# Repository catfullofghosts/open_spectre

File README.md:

# OPEN_SPECTRE ✨
FPGA recreation of the EMS SPECTRE video synth.

Sorry about the repo disappearing for a while. Had some issues, it's back now.

Open to donations and contributors with FPGA experience.

> The EMS Sprectre video synthesiser was a unique and revolutionary product for its time (late 1970's): an instrument capable of producing exciting graphic images on an ordinary television screen. The complete SPECTRE package consists of the synthesiser itself, plus a Sony Trinitron colour monitor and a Sony black-and-white TV camera. The synthesiser was compact (38"x23.5"x7"), portable (about 35 pounds/15.9KG), and unequalled in its simplicity and versatility.

## Status (on an Arty Z7-20)

`overall progress is: it runs!, but still lots of little things to do`

| block | state | notes |
| --- | --- | --- |
| HDMI in / out | done | Digilent Arty Z7-20, input works! output is at 720P |
| digital matrix | done |  |
| analog matrix | done | need to merge signed branch in. |
| oscillators | done | vert sync still a bit blocky, why? |
| shape gen | almost done | needs compare with original|
| colour encode | done | |
| audio in | wip | working, but needs propper testing|
| Vitis test software | done | video in works, frame buffer works, midi parsing works |
| Pico Based midi usb in | done | is just a bridge (computer -> pico (usb midi) -> uart -> zynq |
| hardware interface | not started | still software controlled |

## Aim

Recreate the SPECTRE in HDL so it can stay true to the original design. Then expand on the design in the same spirit as the original.
The idea is preservation, but not at the cost of usability and modern quality of life things (like digital video in and out, or MIDI control)

More on that: [Cloning Hardware Ethos](documentation/Cloning%20a%20process%20not%20a%20device.md)

## FPGA build
- [How to build with Vivado 2024.2 / `build.bat`](fpga/readme.md)

## Want to contribute?

If you have FPGA and/or Verilog/VHDL skills, industrial design skills or VST building skills, I/we would love to have you involved. PLZ!!!!!. A few things first.

### What to do first
- Look through [Spectron Resources](Spectron%20Resources/readme.md) to get an idea of what the EMS SPECTRE is and how it works
- Look at the [top-level diagram](documentation/ems_diagram.drawio) and the [list of modules](documentation/readme.md)
- HDL lives in [`fpga/src`](fpga/src/readme.md) — top is `spector_wrapper_zynq_B.vhd`

### Project details
- RTL in VHDL or Verilog (VHDL preferred, no SystemVerilog sorry)
- One module per file with a separate testbench (Verilog or VHDL testbenches only — not everything has one yet, but it should)
- Testbenches should print a message at the end confirming pass or fail
- No HLS or auto-generated code, no busses or interfaces for now (will be busses later)
- Use any software you like, but a Vivado project is supplied
- Follow the template for file headers and comments
- Follow the folder structure for the project
- Contributions need to be something we can release under CC BY-NC

### How to get involved
- Email *OPEN.SPECTRE.PROJECT@gmail.com* and see what modules/work we need at the moment
- Branch the repo, make a module, and submit a pull request
- If you are not good at git/GitHub, write the module and email it to us. We will integrate it.

## License
Creative Commons CC BY-NC
* I want everyone to be able to experience this seminal (ewwww...) video synth and learn from its design and technical wizardry....... buuuuut, I want to make a physical product version of this one day, so hence the NC. That said if you want to do some thing commercial with this code, just email me about it and I'll most likely just say yes.

## Contributors
- Remi Freer
- Jacob Stoker
- Andrey Demenev
- Robert D Jordan

## Donations
We are very thankful to have received donations from the following people:
Chris Korvin,
Jay Hotchin,
Milton Grimshaw, 
and more amazing anonymous people.

## Thank yous
- MESS Melbourne
  - Sam Galyer
  - Robin Fox
- Flo Kaufmann
- Violet Shylet

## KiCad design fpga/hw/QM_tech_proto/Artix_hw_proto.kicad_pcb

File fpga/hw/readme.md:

using this dev board:
https://www.aliexpress.com/item/1005005961199362.html?spm=a2g0o.order_list.order_list_main.76.1cc71802oC4QSS
https://github.com/ChinaQMTECH/QMTECH_XC7A15T_35T_CSG325_CORE_BOARD

use these libs
https://github.com/jmwilson/Adafruit-GFX-Library_MicroBlaze
https://github.com/jmwilson/Adafruit_SSD1306_MicroBlaze

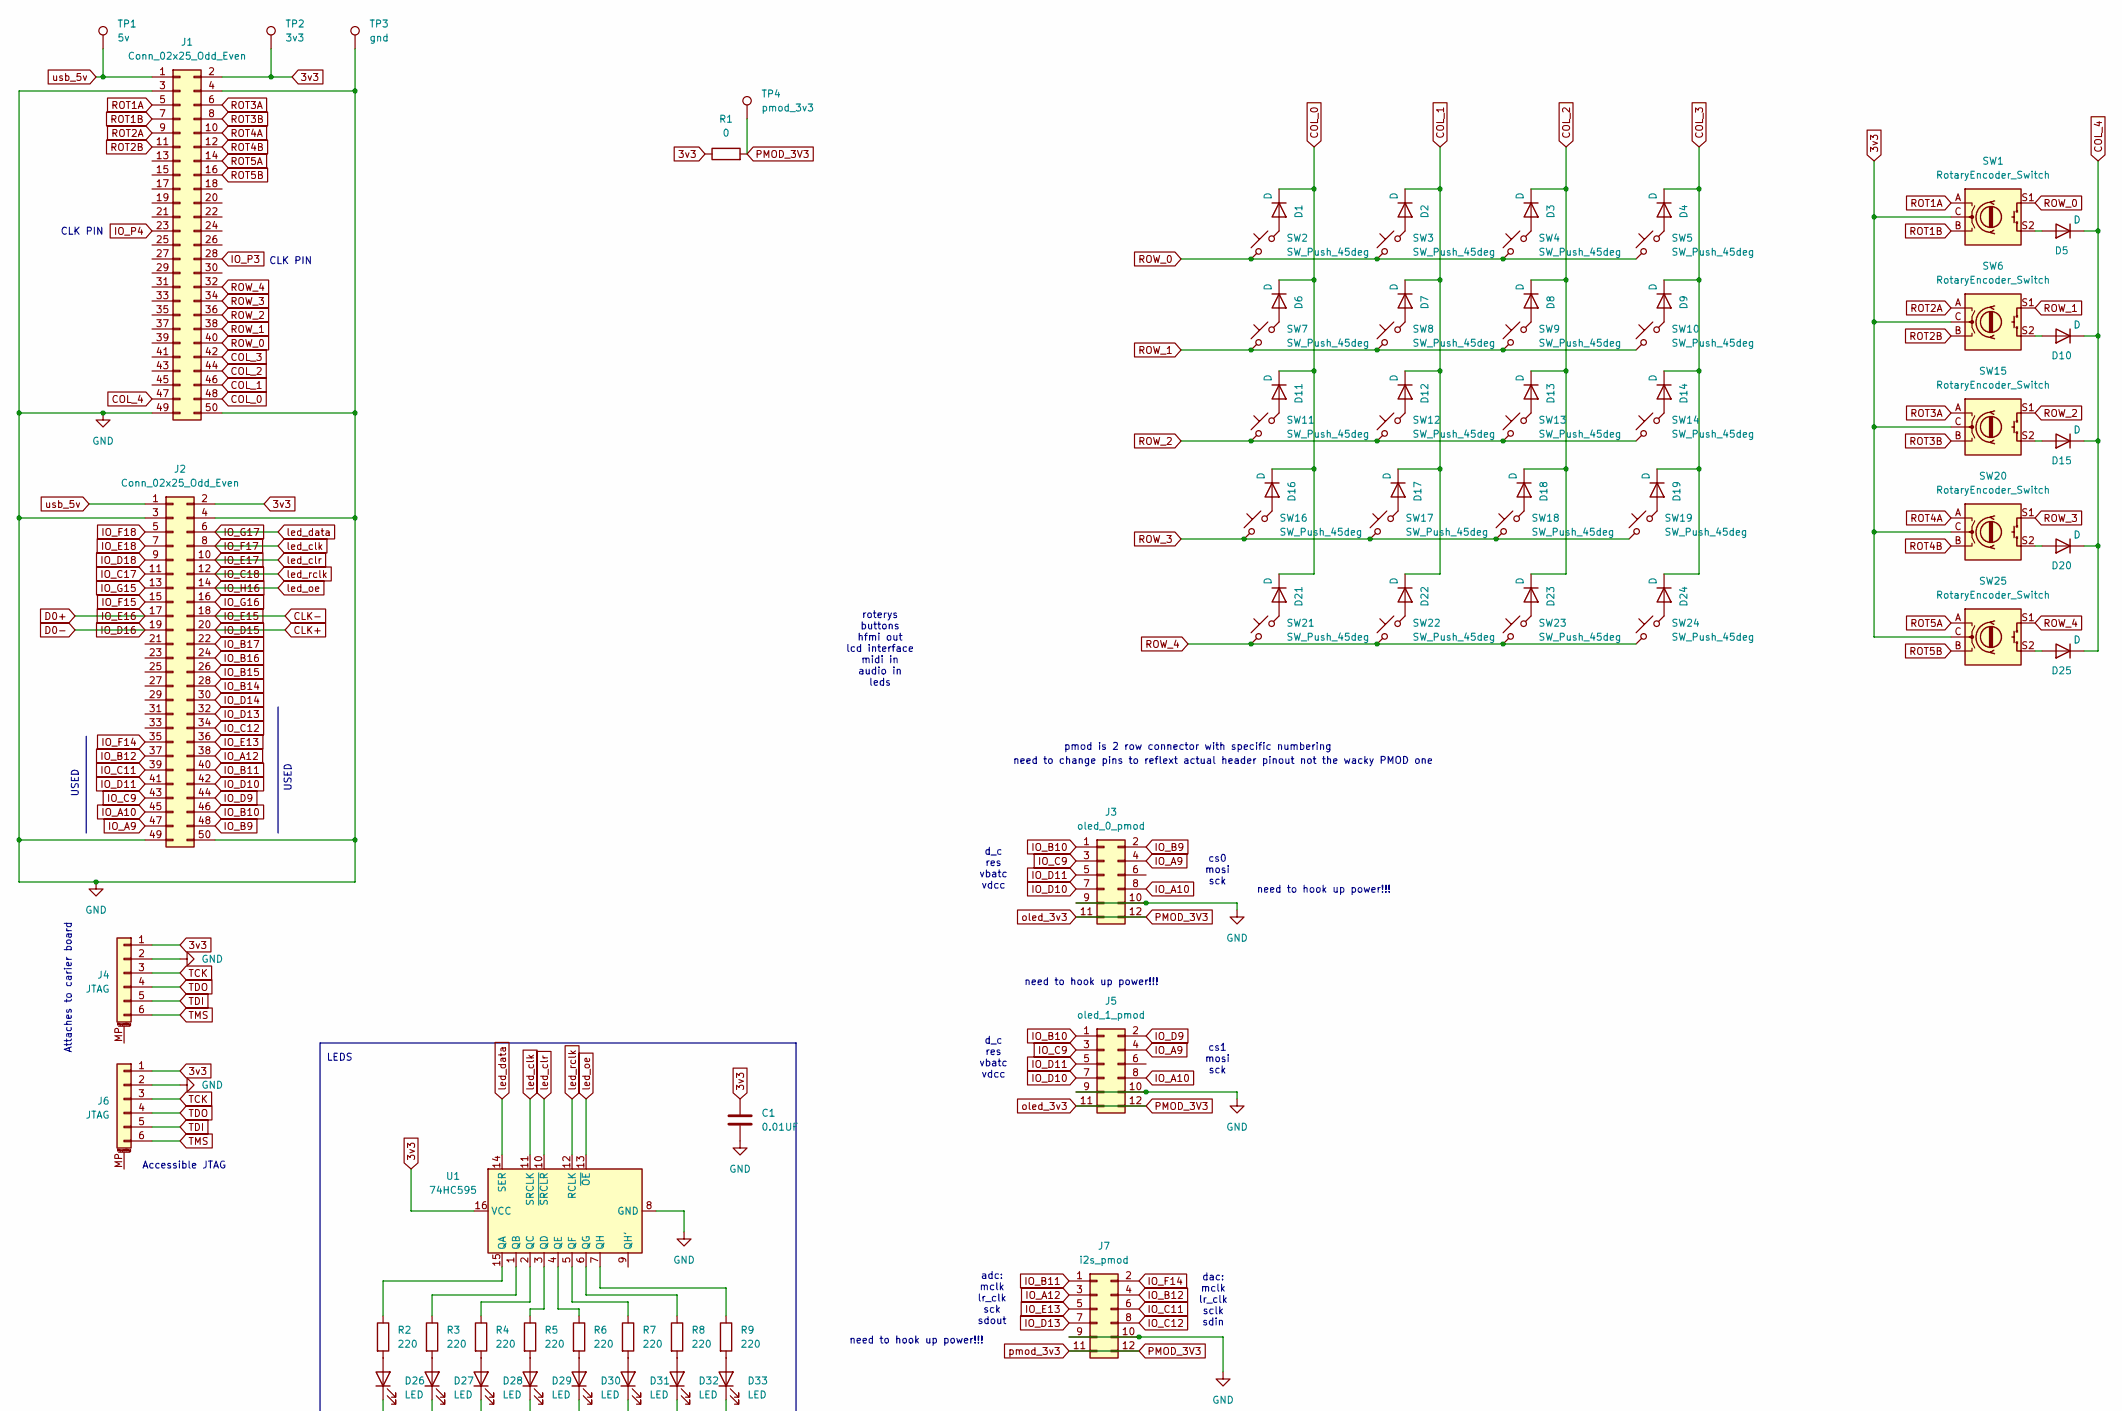
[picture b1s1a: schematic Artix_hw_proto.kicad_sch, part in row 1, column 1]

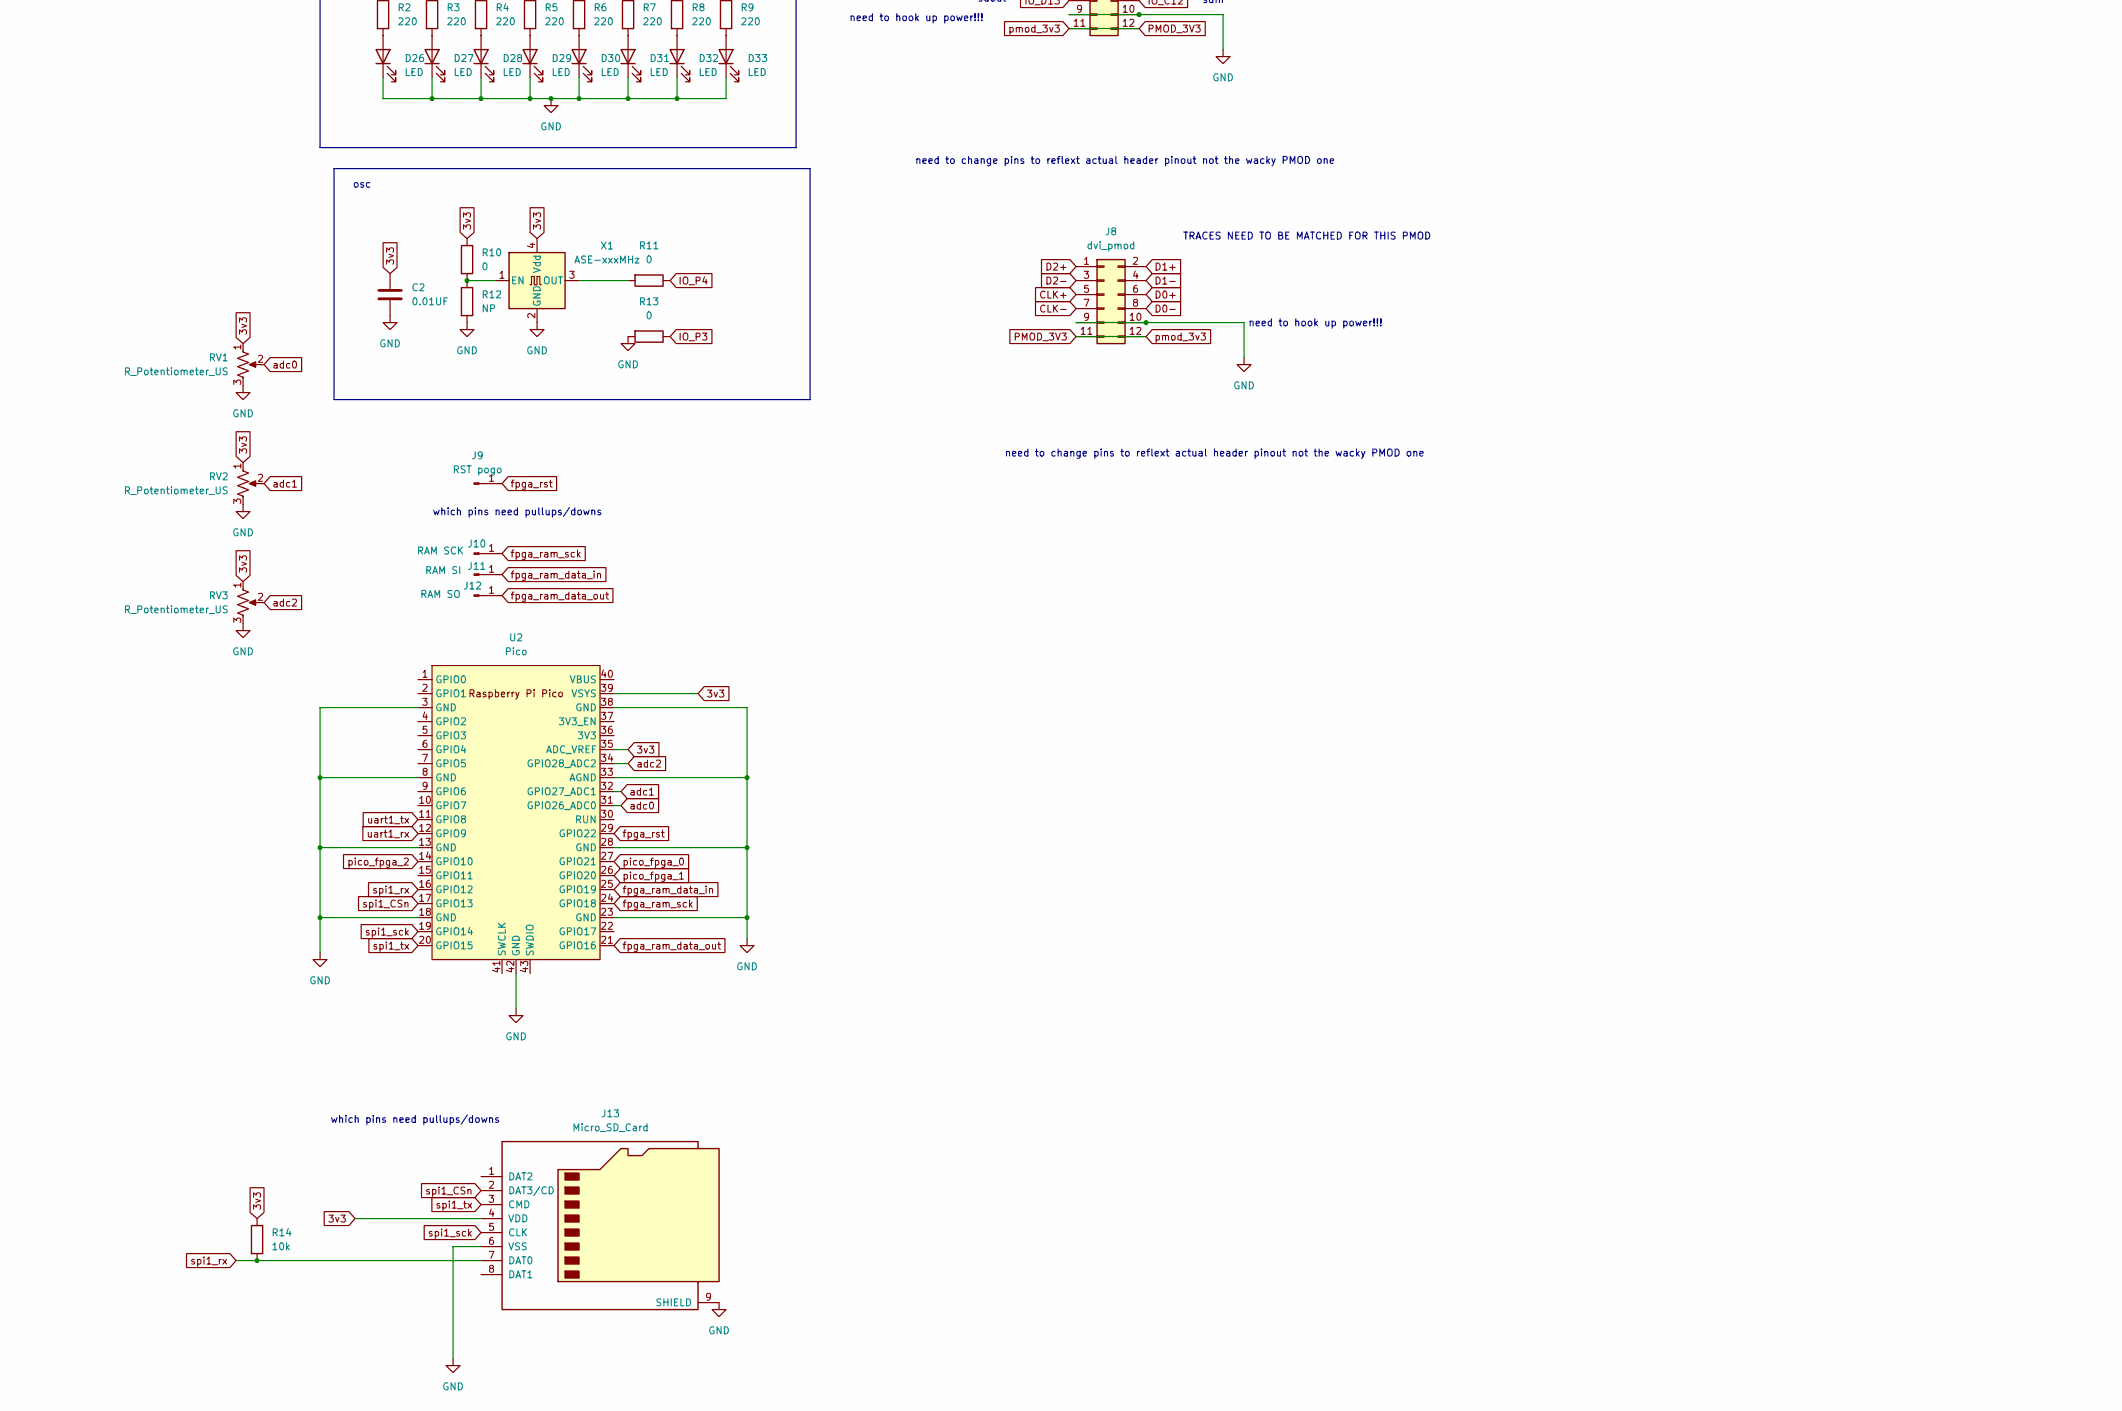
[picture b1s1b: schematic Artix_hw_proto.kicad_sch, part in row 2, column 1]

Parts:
C1, C2: 0.01UF; C_Axial_L3.8mm_D2.6mm_P7.50mm_Horizontal
D1, D2, D3, D4, D5, D6, D7, D8, D9, D10, D11, D12, D13, D14, D15, D16, D17, D18, D19, D20, D21, D22, D23, D24, D25: D; D_MELF-RM10_Universal_Handsoldering
D26, D27, D28, D29, D30, D31, D32, D33: LED; LED_D3.0mm_FlatTop
J1, J2: Conn_02x25_Odd_Even; PinSocket_2x25_P2.54mm_Vertical
J3: oled_0_pmod; PinSocket_2x06_P2.54mm_Horizontal
J4, J6: JTAG; PinHeader_1x06_P2.54mm_Vertical
J5: oled_1_pmod; PinSocket_2x06_P2.54mm_Horizontal
J7: i2s_pmod; PinSocket_2x06_P2.54mm_Horizontal
J8: dvi_pmod; PinSocket_2x06_P2.54mm_Horizontal
J9: RST pogo; PinHeader_1x01_P2.54mm_Vertical
J10: RAM SCK; PinHeader_1x01_P2.54mm_Vertical
J11: RAM SI; PinHeader_1x01_P2.54mm_Vertical
J12: RAM SO; PinHeader_1x01_P2.54mm_Vertical
J13: Micro_SD_Card; microSD_HC_Wuerth_693072010801
R1, R10, R11, R13: 0; R_0805_2012Metric_Pad1.20x1.40mm_HandSolder
R2, R3, R4, R5, R6, R7, R8, R9: 220; R_0805_2012Metric_Pad1.20x1.40mm_HandSolder
R12: NP; R_0805_2012Metric_Pad1.20x1.40mm_HandSolder
R14: 10k; R_0805_2012Metric_Pad1.20x1.40mm_HandSolder
RV1, RV2, RV3: R_Potentiometer_US; Potentiometer_Alpha_RD901F-40-00D_Single_Vertical_CircularH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
SW1, SW6, SW15, SW20, SW25: RotaryEncoder_Switch; RotaryEncoder_Alps_EC11E-Switch_Vertical_H20mm
SW2, SW3, SW4, SW5, SW7, SW8, SW9, SW10, SW11, SW12, SW13, SW14, SW16, SW17, SW18, SW19, SW21, SW22, SW23, SW24: SW_Push_45deg; SW_PUSH_6mm
TP1: 5v; TestPoint_Loop_D1.80mm_Drill1.0mm_Beaded
TP2: 3v3; TestPoint_Loop_D1.80mm_Drill1.0mm_Beaded
TP3: gnd; TestPoint_Loop_D1.80mm_Drill1.0mm_Beaded
TP4: pmod_3v3; TestPoint_Loop_D1.80mm_Drill1.0mm_Beaded
U1: 74HC595; DIP-16_W7.62mm_SMDSocket_SmallPads
U2: Pico; RPi_Pico_SMD_TH
X1: ASE-xxxMHz; Oscillator_SMD_Abracon_ASE-4Pin_3.2x2.5mm

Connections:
3v3: C1.1, C2.1, J1.2, J2.2, J4.1, J6.1, J13.4 (VDD), R1.1, R10.1, R14.1, RV1.1, RV2.1, RV3.1, SW1.C, SW6.C, SW15.C, SW20.C, SW25.C, TP2.1, U1.16 (VCC), U2.35 (ADC_VREF), U2.39 (VSYS), X1.4 (Vdd)
CLK+: J2.20, J8.5
CLK-: J2.18, J8.7
COL_0: D1.1 (K), D6.1 (K), D11.1 (K), D16.1 (K), D21.1 (K), J1.48
COL_1: D2.1 (K), D7.1 (K), D12.1 (K), D17.1 (K), D22.1 (K), J1.46
COL_2: D3.1 (K), D8.1 (K), D13.1 (K), D18.1 (K), D23.1 (K), J1.44
COL_3: D4.1 (K), D9.1 (K), D14.1 (K), D19.1 (K), D24.1 (K), J1.42
COL_4: D5.1 (K), D10.1 (K), D15.1 (K), D20.1 (K), D25.1 (K), J1.47
D0+: J2.17, J8.6
D0-: J2.19, J8.8
D1+: J8.2
D1-: J8.4
D2+: J8.1
D2-: J8.3
GND: C1.2, C2.2, D26.1 (K), D27.1 (K), D28.1 (K), D29.1 (K), D30.1 (K), D31.1 (K), D32.1 (K), D33.1 (K), J1.3, J1.4, J1.49, J1.50, J2.3, J2.4, J2.49, J2.50, J3.9, J3.10, J4.2, J5.9, J5.10, J6.2, J7.9, J7.10, J8.9, J8.10, J13.6 (VSS), J13.9 (SHIELD), R12.2, R13.2, RV1.3, RV2.3, RV3.3, TP3.1, U1.8 (GND), U2.3 (GND), U2.8 (GND), U2.13 (GND), U2.18 (GND), U2.23 (GND), U2.28 (GND), U2.33 (AGND), U2.38 (GND), U2.42 (GND), X1.2 (GND)
IO_A9: J2.47, J3.4, J5.4
IO_A10: J2.45, J3.8, J5.8
IO_A12: J2.38, J7.3
IO_B9: J2.48, J3.2
IO_B10: J2.46, J3.1, J5.1
IO_B11: J2.40, J7.1
IO_B12: J2.37, J7.4
IO_B14: J2.28
IO_B15: J2.26
IO_B16: J2.24
IO_B17: J2.22
IO_C9: J2.43, J3.3, J5.3
IO_C11: J2.39, J7.6
IO_C12: J2.34, J7.8
IO_C17: J2.11
IO_C18: J2.12, U1.12 (RCLK)
IO_D9: J2.44, J5.2
IO_D10: J2.42, J3.7, J5.7
IO_D11: J2.41, J3.5, J5.5
IO_D13: J2.32, J7.7
IO_D14: J2.30
IO_D18: J2.9
IO_E13: J2.36, J7.5
IO_E17: J2.10, U1.10 (~SRCLR)
IO_E18: J2.7
IO_F14: J2.35, J7.2
IO_F15: J2.15
IO_F17: J2.8, U1.11 (SRCLK)
IO_F18: J2.5
IO_G15: J2.13
IO_G16: J2.16
IO_G17: J2.6, U1.14 (SER)
IO_H16: J2.14, U1.13 (~OE)
IO_P3: J1.28, R13.1
IO_P4: J1.23, R11.1
unnamed: D1.2 (A), SW2.2
unnamed: D2.2 (A), SW3.2
unnamed: D3.2 (A), SW4.2
unnamed: D4.2 (A), SW5.2
unnamed: D5.2 (A), SW1.S2
unnamed: D6.2 (A), SW7.2
unnamed: D7.2 (A), SW8.2
unnamed: D8.2 (A), SW9.2
unnamed: D9.2 (A), SW10.2
unnamed: D10.2 (A), SW6.S2
unnamed: D11.2 (A), SW11.2
unnamed: D12.2 (A), SW12.2
unnamed: D13.2 (A), SW13.2
unnamed: D14.2 (A), SW14.2
unnamed: D15.2 (A), SW15.S2
unnamed: D16.2 (A), SW16.2
unnamed: D17.2 (A), SW17.2
unnamed: D18.2 (A), SW18.2
unnamed: D19.2 (A), SW19.2
unnamed: D20.2 (A), SW20.S2
unnamed: D21.2 (A), SW21.2
unnamed: D22.2 (A), SW22.2
unnamed: D23.2 (A), SW23.2
unnamed: D24.2 (A), SW24.2
unnamed: D25.2 (A), SW25.S2
unnamed: D26.2 (A), R2.2
unnamed: D27.2 (A), R3.2
unnamed: D28.2 (A), R4.2
unnamed: D29.2 (A), R5.2
unnamed: D30.2 (A), R6.2
unnamed: D31.2 (A), R7.2
unnamed: D32.2 (A), R8.2
unnamed: D33.2 (A), R9.2
unnamed: R2.1, U1.15 (QA)
unnamed: R3.1, U1.1 (QB)
unnamed: R4.1, U1.2 (QC)
unnamed: R5.1, U1.3 (QD)
unnamed: R6.1, U1.4 (QE)
unnamed: R7.1, U1.5 (QF)
unnamed: R8.1, U1.6 (QG)
unnamed: R9.1, U1.7 (QH)
unnamed: R10.2, R12.1, X1.1 (EN)
unnamed: R11.2, X1.3 (OUT)
PMOD_3V3: J3.11, J3.12, J5.11, J5.12, J7.11, J7.12, J8.11, J8.12, R1.2, TP4.1
ROT1A: J1.5, SW1.A
ROT1B: J1.7, SW1.B
ROT2A: J1.9, SW6.A
ROT2B: J1.11, SW6.B
ROT3A: J1.6, SW15.A
ROT3B: J1.8, SW15.B
ROT4A: J1.10, SW20.A
ROT4B: J1.12, SW20.B
ROT5A: J1.14, SW25.A
ROT5B: J1.16, SW25.B
ROW_0: J1.40, SW1.S1, SW2.1, SW3.1, SW4.1, SW5.1
ROW_1: J1.38, SW6.S1, SW7.1, SW8.1, SW9.1, SW10.1
ROW_2: J1.36, SW11.1, SW12.1, SW13.1, SW14.1, SW15.S1
ROW_3: J1.34, SW16.1, SW17.1, SW18.1, SW19.1, SW20.S1
ROW_4: J1.32, SW21.1, SW22.1, SW23.1, SW24.1, SW25.S1
TCK: J4.3, J6.3
TDI: J4.5, J6.5
TDO: J4.4, J6.4
TMS: J4.6, J6.6
adc0: RV1.2, U2.31 (GPIO26_ADC0)
adc1: RV2.2, U2.32 (GPIO27_ADC1)
adc2: RV3.2, U2.34 (GPIO28_ADC2)
fpga_ram_data_in: J11.1, U2.25 (GPIO19)
fpga_ram_data_out: J12.1, U2.21 (GPIO16)
fpga_ram_sck: J10.1, U2.24 (GPIO18)
fpga_rst: J9.1, U2.29 (GPIO22)
pico_fpga_0: U2.27 (GPIO21)
pico_fpga_1: U2.26 (GPIO20)
pico_fpga_2: U2.14 (GPIO10)
spi1_CSn: J13.2 (DAT3/CD), U2.17 (GPIO13)
spi1_rx: J13.7 (DAT0), R14.2, U2.16 (GPIO12)
spi1_sck: J13.5 (CLK), U2.19 (GPIO14)
spi1_tx: J13.3 (CMD), U2.20 (GPIO15)
uart1_rx: U2.12 (GPIO9)
uart1_tx: U2.11 (GPIO8)
usb_5v: J1.1, J2.1, TP1.1

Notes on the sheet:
cs0 mosi sck
need to change pins to reflext actual header pinout not the wacky PMOD one
need to hook up power!!!
TRACES NEED TO BE MATCHED FOR THIS PMOD
Attaches to carier board
which pins need pullups/downs
dac: mclk lr_clk sclk sdin
cs1 mosi sck
adc: mclk lr_clk sck sdout
d_c res vbatc vdcc
roterys buttons hfmi out lcd interface midi in audio in leds
CLK PIN
LEDS
osc
USED
pmod is 2 row connector with specific numbering
Accessible JTAG

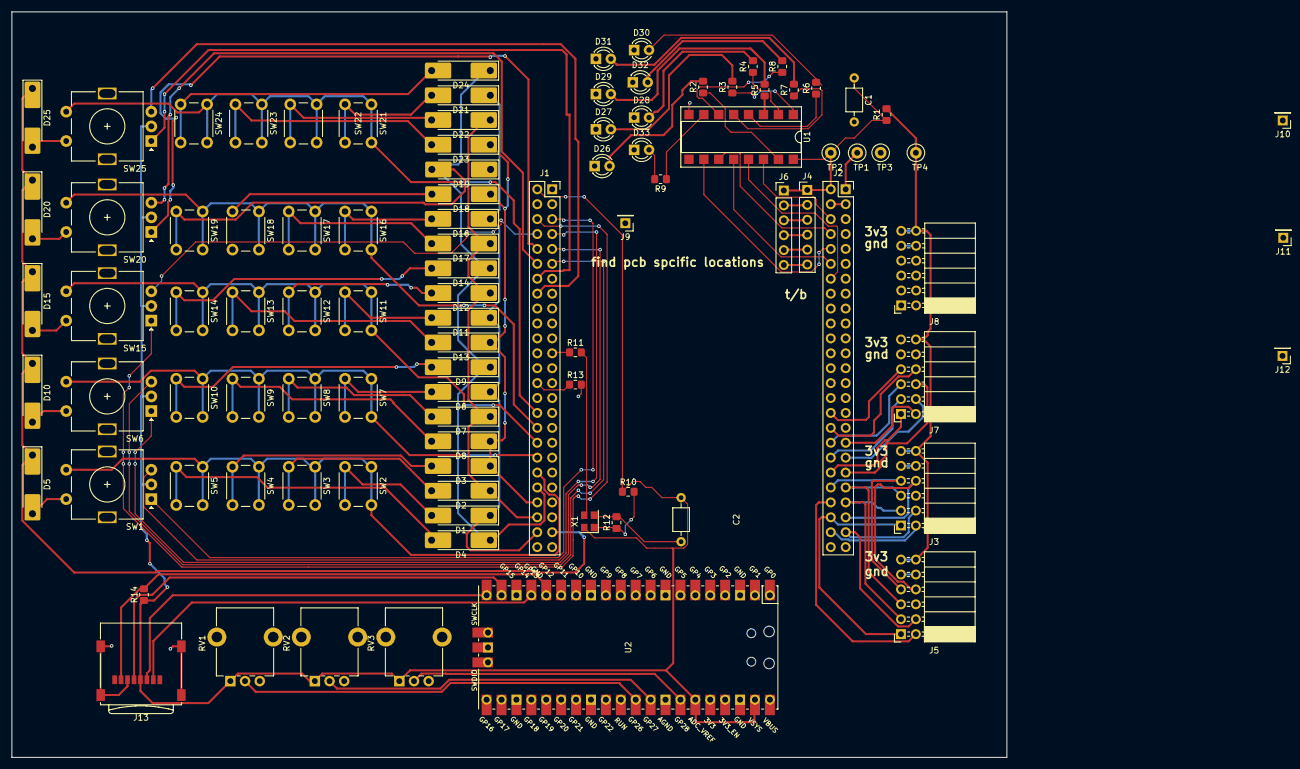
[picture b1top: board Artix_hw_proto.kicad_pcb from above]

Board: 2 copper layers, 169.5 x 127.0 mm, 97 parts (0 on the bottom side), 109 nets.

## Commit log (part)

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2026-06-02 backup of openspector from other account
2026-06-16 moved unused vhdl away to make building easyer/faster
2026-06-17 minor code updates, added in 2nd shape gen, fixed some errors and doubleups in the analoge side matrix
2026-06-17 800us delay done with bram, its a waste but hey thats life
2026-06-17 added IP repo properly, removed previous IP as unzipped package
2026-06-17 started oputput video fx on a pixel by pixel basis
2026-06-17 added dithering fx
2026-06-18 sharp and chormatic abrasion added as effects
2026-06-18 added 8 sprites with position and hard transperency that can get muxed over the output, full rgb control
2026-06-25 sprites added from sprite project. also added analisis and hasing module analisis could be used for midi out? and hash could be used for automated testing
